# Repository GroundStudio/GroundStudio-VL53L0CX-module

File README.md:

GroundStudio Time of Flight Distance Sensor module
====================================

Get it from [ardushop.ro](https://ardushop.ro/ro/home/2515-modul-vl53l0x-senzor-de-distanta-groundstudio.html)

Explore all the GroundStudio products at [GroundStudio.ro](https://groundstudio.ro/)

Description
-------------------
Time of Flight Distance Sensor module based on VL53L0CX sensor chip.

Contents
-------------------

* [/Documentation](https://github.com/GroundStudio/GroundStudio-VL53L0CX-module/tree/main/Documentation) -- Contains documentation written during creation of this repository, with readme.md index of its own!
* [/Firmware](https://github.com/GroundStudio/GroundStudio-VL53L0CX-module/tree/main/Firmware) -- Firmware (bootloaders, etc)
* [/Hardware](https://github.com/GroundStudio/GroundStudio-VL53L0CX-module/tree/main/Hardware) -- Schematics, layout.
* [/Libraries](https://github.com/GroundStudio/GroundStudio-VL53L0CX-module/tree/main/Libraries) -- Arduino/CircuitPython libraries. 
* [/Tools](https://github.com/GroundStudio/GroundStudio-VL53L0CX-module/tree/main) -- Tools needed for compiling, uploading bootloader, etc.

Versions
-------------------
*(Not all tags shown)*
* [V0.0.1] Initial version

License
-------------------

This is released under the [Attribution-ShareAlike 4.0 International (CC BY-SA 4.0)](https://creativecommons.org/licenses/by-sa/4.0/) license. 
**You are welcome to use this for commercial purposes.**

Please consider contributing back to this project or others to help the open-source hardware community continue to thrive and grow! 

Certifications:

[Open Source Hardware Association](https://certification.oshwa.org/ro000010.html)   
   
[
](https://certification.oshwa.org/ro000010.html)

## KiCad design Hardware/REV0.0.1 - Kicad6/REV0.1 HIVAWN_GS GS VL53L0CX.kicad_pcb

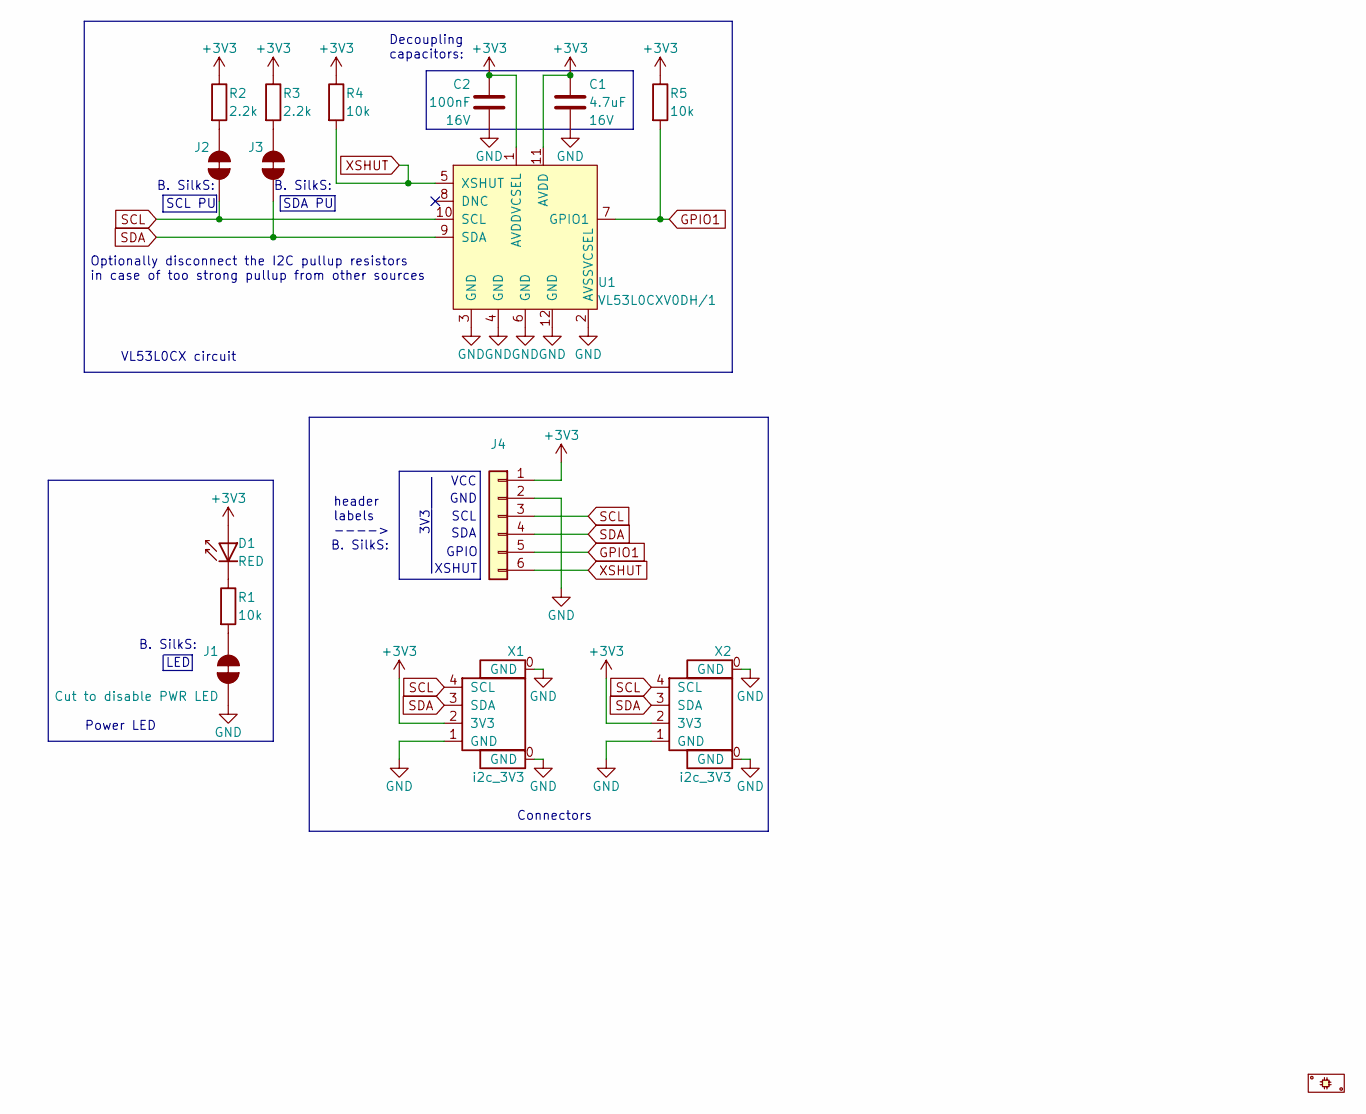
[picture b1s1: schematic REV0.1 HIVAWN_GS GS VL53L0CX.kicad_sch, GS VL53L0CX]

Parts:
C1: C_0402_4.7uF_16V; C_0402; Rated voltage 16V; MPN C0402X5R475M160NT; LCSC C729453
C2: C_0402_100nF_16V; C_0402; Rated voltage 16V; MPN 0402B104K160CT; LCSC C83056
D1: LED_0402_RED; LED_0402; MPN TZ-P2-0402RTIA1-0.45T; LCSC C779449
J1: Cut to disable PWR LED; SolderJumper_NC
J2, J3: SolderJumper_NC
J4: PinHeader_1x06_P2.54_V_M; PinHeader_1x06_P2.54mm_Vertical_Male; MPN C37208; LCSC C37208
P1: PCB; MPN HIVAWN_GS_PCB
R1, R4, R5: R_0402_10k; R_0402; MPN 0402WGJ0103TCE; LCSC C25531
R2, R3: R_0402_2.2k; R_0402; MPN RC-02W2201FT; LCSC C258093
U1: VL53L0CXV0DH/1; VL53L0CXV0DH_1; MPN VL53L0CXV0DH/1; Digi-Key_PN 497-16538-1-ND
X1, X2: SH_1x04_P1.0_H; SH__1x04_P1.00mm_Horizontal; MPN C145956; LCSC C145956

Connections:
+3V3: C1.1, C2.2, D1.2 (A), J4.1, R2.1, R3.1, R4.1, R5.1, U1.1 (AVDDVCSEL), U1.11 (AVDD), X1.2 (3V3), X2.2 (3V3)
GND: C1.2, C2.1, J1.1, J4.2, U1.2 (AVSSVCSEL), U1.3 (GND), U1.4 (GND), U1.6 (GND), U1.12 (GND), X1.0 (GND), X1.1 (GND), X2.0 (GND), X2.1 (GND)
GPIO1: J4.5, R5.2, U1.7 (GPIO1)
unnamed: D1.1 (K), R1.1
unnamed: J1.2, R1.2
unnamed: J2.2, R2.2
unnamed: J3.2, R3.2
SCL: J2.1, J4.3, U1.10 (SCL), X1.4 (SCL), X2.4 (SCL)
SDA: J3.1, J4.4, U1.9 (SDA), X1.3 (SDA), X2.3 (SDA)
XSHUT: J4.6, R4.2, U1.5 (XSHUT)

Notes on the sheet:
Power LED
XSHUT
B. SilkS:
Optionally disconnect the I2C pullup resistors in case of too strong pullup from other sources
header labels ---->
VL53L0CX circuit
SCL
GND
Connectors
SDA PU
LED
VCC
GPIO
Decoupling capacitors:
3V3
SCL PU
SDA

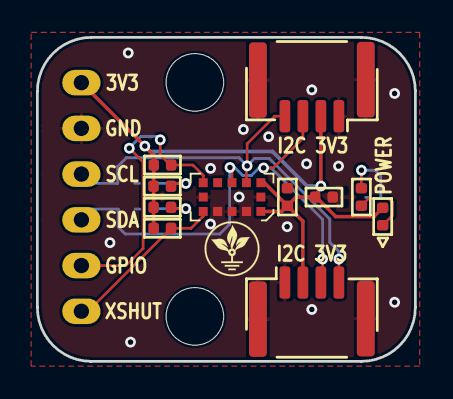
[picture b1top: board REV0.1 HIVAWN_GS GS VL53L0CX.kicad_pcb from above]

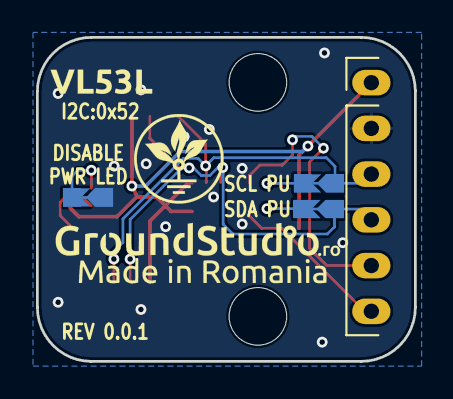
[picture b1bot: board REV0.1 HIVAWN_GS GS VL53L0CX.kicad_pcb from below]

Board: 2 copper layers, 21.0 x 18.0 mm, 15 parts (4 on the bottom side), 10 nets.

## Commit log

2023-10-23 - first commit
2023-10-24 - added datasheet and kicad 6 files
2023-11-03 - added datasheet
